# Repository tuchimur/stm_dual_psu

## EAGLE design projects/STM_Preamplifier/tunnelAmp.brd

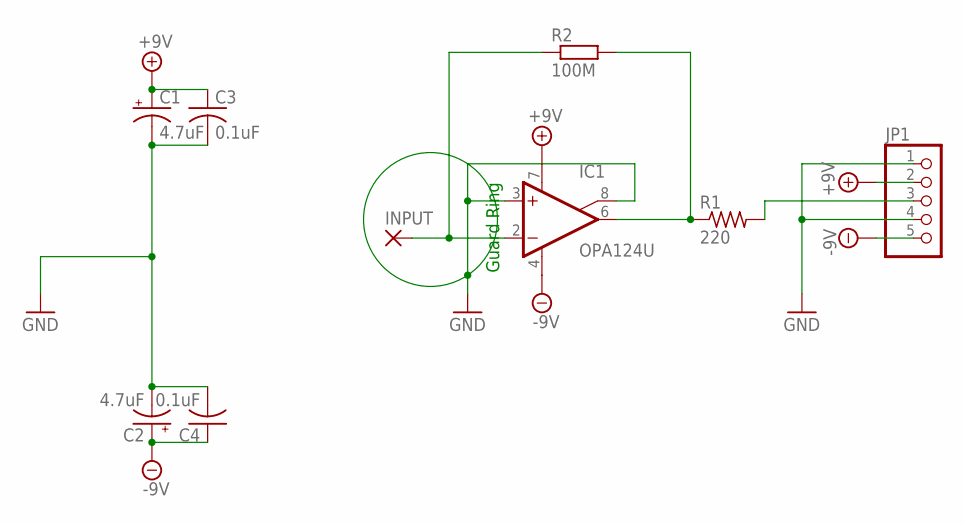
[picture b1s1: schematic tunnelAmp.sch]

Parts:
C1, C2: 4.7uF; C/6032-28W
C3, C4: 0.1uF; C0603
IC1: OPA124U; SO08
INPUT: 2,54/1,1
JP1: PINHD-1X5; 1X05
R1: 220; R0603
R2: 100M; R1206

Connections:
+9V: C1.+, C3.1, IC1.7 (V+), JP1.2
-9V: C2.+, C4.1, IC1.4 (V-), JP1.5
GND: C1.-, C2.-, C3.2, C4.2, IC1.3 (+IN), IC1.8 (SUBS), JP1.1, JP1.4
unnamed: IC1.6 (OUT), R1.1, R2.2
unnamed: JP1.3, R1.2
unnamed: IC1.2 (-IN), INPUT.1, R2.1

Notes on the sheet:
Guard Ring

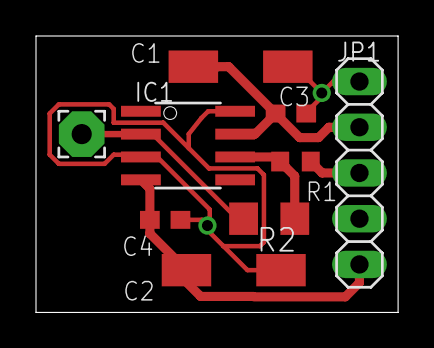
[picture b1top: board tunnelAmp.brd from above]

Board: 2 copper layers, 20.1 x 15.4 mm, 9 parts (0 on the bottom side), 6 nets.

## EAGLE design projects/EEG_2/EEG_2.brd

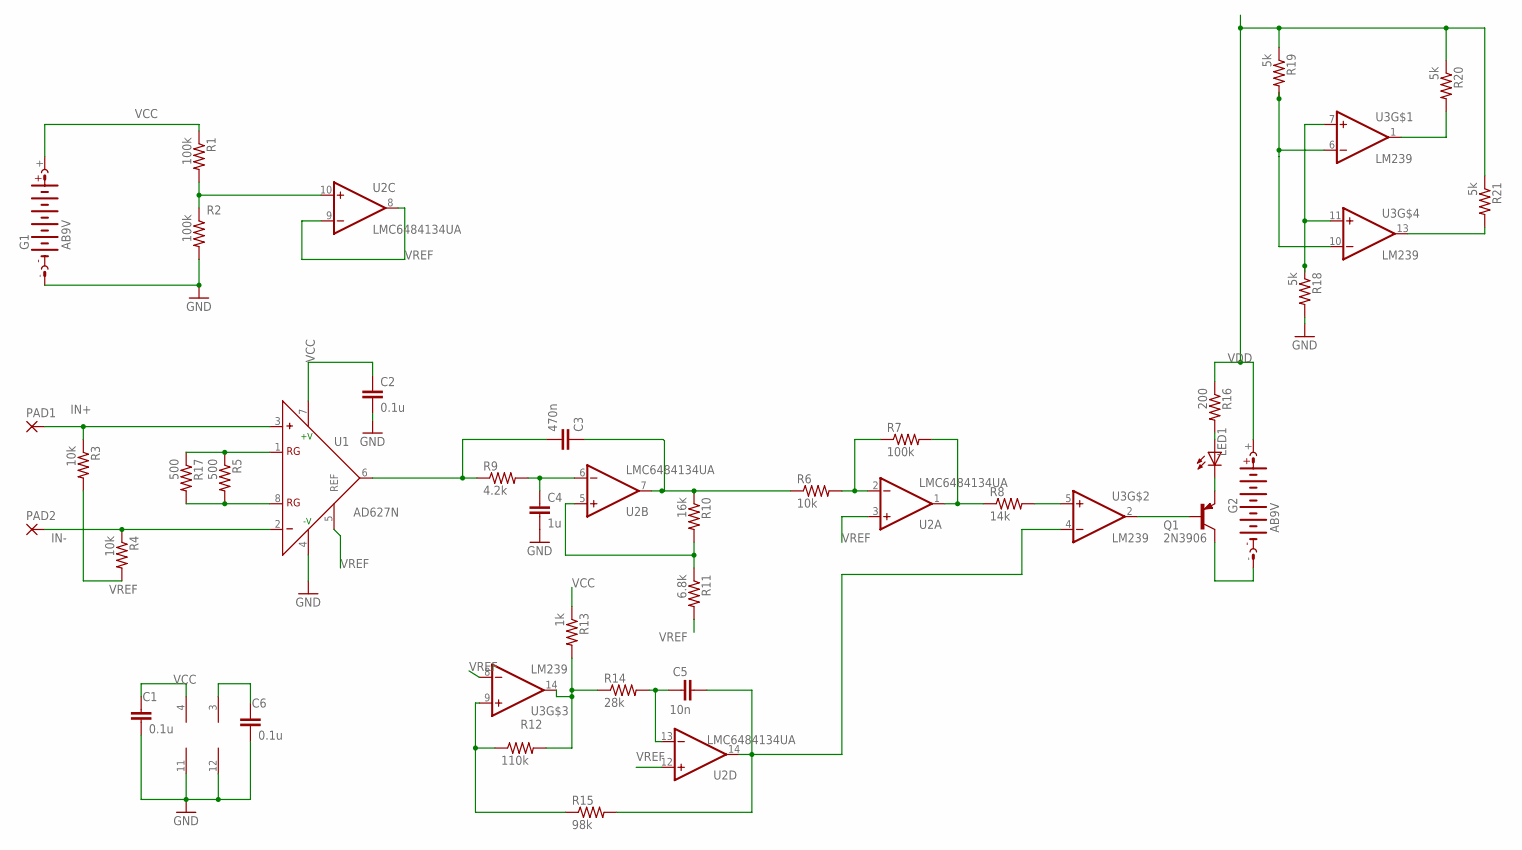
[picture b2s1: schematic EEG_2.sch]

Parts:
C1, C2, C6: 0.1u; C5B3
C3: 470n; C5B3
C4: 1u; C5B3
C5: 10n; C5B3
G1, G2: AB9V
LED1: LED5MM
PAD1, PAD2: 2,15/1,0
Q1: 2N3906; TO92
R1, R2, R7: 100k; 0207/7
R3, R4, R6: 10k; 0207/7
R5, R17: 500; 0207/7
R8: 14k; 0207/7
R9: 4.2k; 0207/7
R10: 16k; 0207/7
R11: 6.8k; 0207/7
R12: 110k; 0207/7
R13: 1k; 0207/7
R14: 28k; 0207/7
R15: 98k; 0207/7
R16: 200; 0207/7
R18, R19, R20, R21: 5k; 0207/7
U1: AD627N; DIL08
U2: LMC6484134UA; SO14
U3: LM239; SO14

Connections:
GND: C1.2, C2.2, C4.2, C6.2, G1.-, R2.2, R18.2, U1.4 (-V), U2.11 (V-), U3.12 (V-)
HELP: R1.2, R2.1, U2.10 (+IN)
IN+: PAD1.1, R3.1, U1.3 (+)
IN-: PAD2.1, R4.1, U1.2 (-)
unnamed: R6.2, R7.1, U2.2 (-IN)
unnamed: R20.2, U3.1 (OUT)
unnamed: C3.1, R9.1, U1.6 (OUT)
unnamed: R5.1, R17.1, U1.1 (RG)
unnamed: R7.2, R8.1, U2.1 (OUT)
unnamed: R5.2, R17.2, U1.8 (RG)
unnamed: R10.2, R11.1, U2.5 (+IN)
unnamed: C4.1, R9.2, U2.6 (-IN)
unnamed: C5.2, R14.2, U2.13 (-IN)
unnamed: R12.1, R15.1, U3.9 (+IN)
unnamed: R12.2, R13.2, R14.1, U3.14 (OUT)
unnamed: LED1.K (C), Q1.3 (E)
unnamed: C5.1, R15.2, U2.14 (OUT), U3.4 (-IN)
unnamed: LED1.A, R16.2
unnamed: R19.2, U3.6 (-IN), U3.10 (-IN)
unnamed: Q1.2 (B), U3.2 (OUT)
unnamed: R18.1, U3.7 (+IN), U3.11 (+IN)
unnamed: R8.2, U3.5 (+IN)
unnamed: R21.2, U3.13 (OUT)
unnamed: G2.-, Q1.1 (C)
unnamed: C3.2, R6.1, R10.1, U2.7 (OUT)
VCC: C1.1, C2.1, G1.+, R1.1, R13.1, U1.7 (+V), U2.4 (V+)
VREF: R3.2, R4.2, R11.2, U1.5 (REF), U2.3 (+IN), U2.8 (OUT), U2.9 (-IN), U2.12 (+IN), U3.8 (-IN)

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
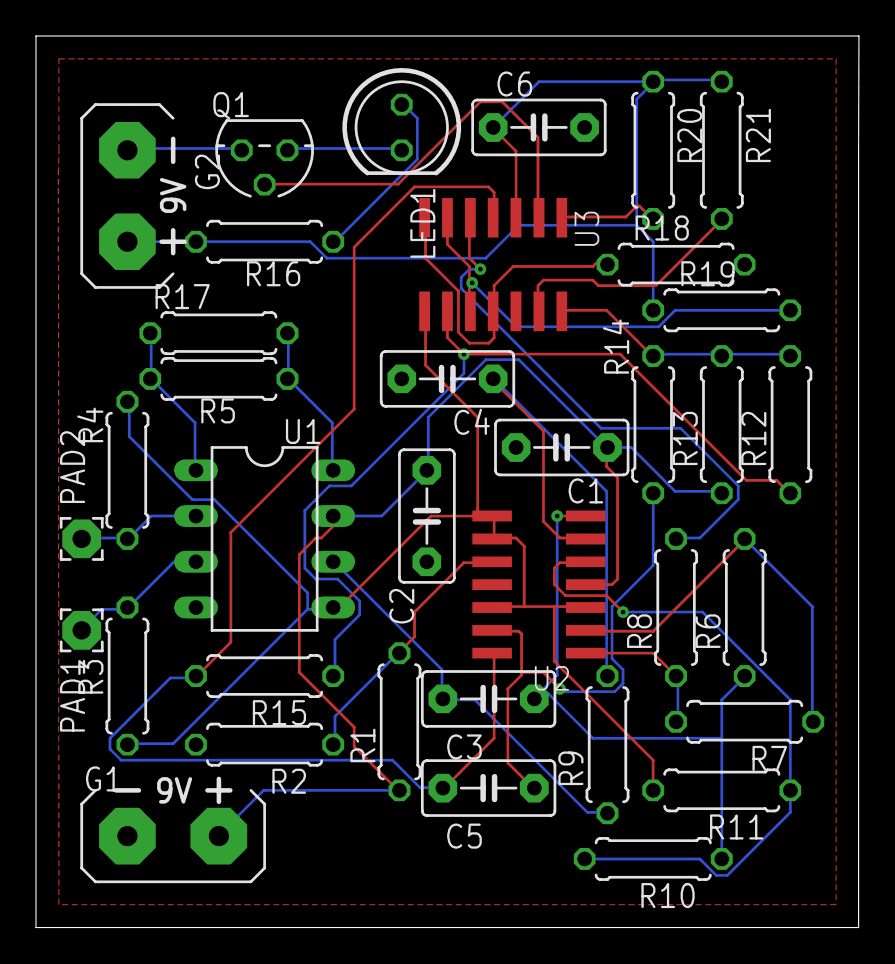
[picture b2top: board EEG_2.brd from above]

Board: 2 copper layers, 45.7 x 49.5 mm, 36 parts (0 on the bottom side), 28 nets.
